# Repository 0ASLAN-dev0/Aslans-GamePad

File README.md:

# **Aslan's GamepPad**
## **Introduction**

This is a little macropad I made, It consists of a Xiao RP2040, Four  Cherry MX Switches and 2 RGB LEDs, Its basically a little rgb keyboard that consits of only four keys that i've coded to be WASD thou that can be changed from the code, The 2 RGB LEDs circle through the color wheel in a smooth animation and to give a sense of feedback each key is assigned a color that shows up when that key is pressed. Thats it :).

---

## **Required Parts**

1x Seeed XIAO RP2040 DIP,
4x Cherry MX-Style switches (Green preferably),
4x Blank DSA Keycaps,
2x SK6812 MINI-E LEDs,
4x M3x16mm screws,
1x 3D printed case (consists of two parts),
1x Soldering Iron/Kit,
1x PCB.

---

## **Images**

### **Render**

### **Schematic**

### **PCB**

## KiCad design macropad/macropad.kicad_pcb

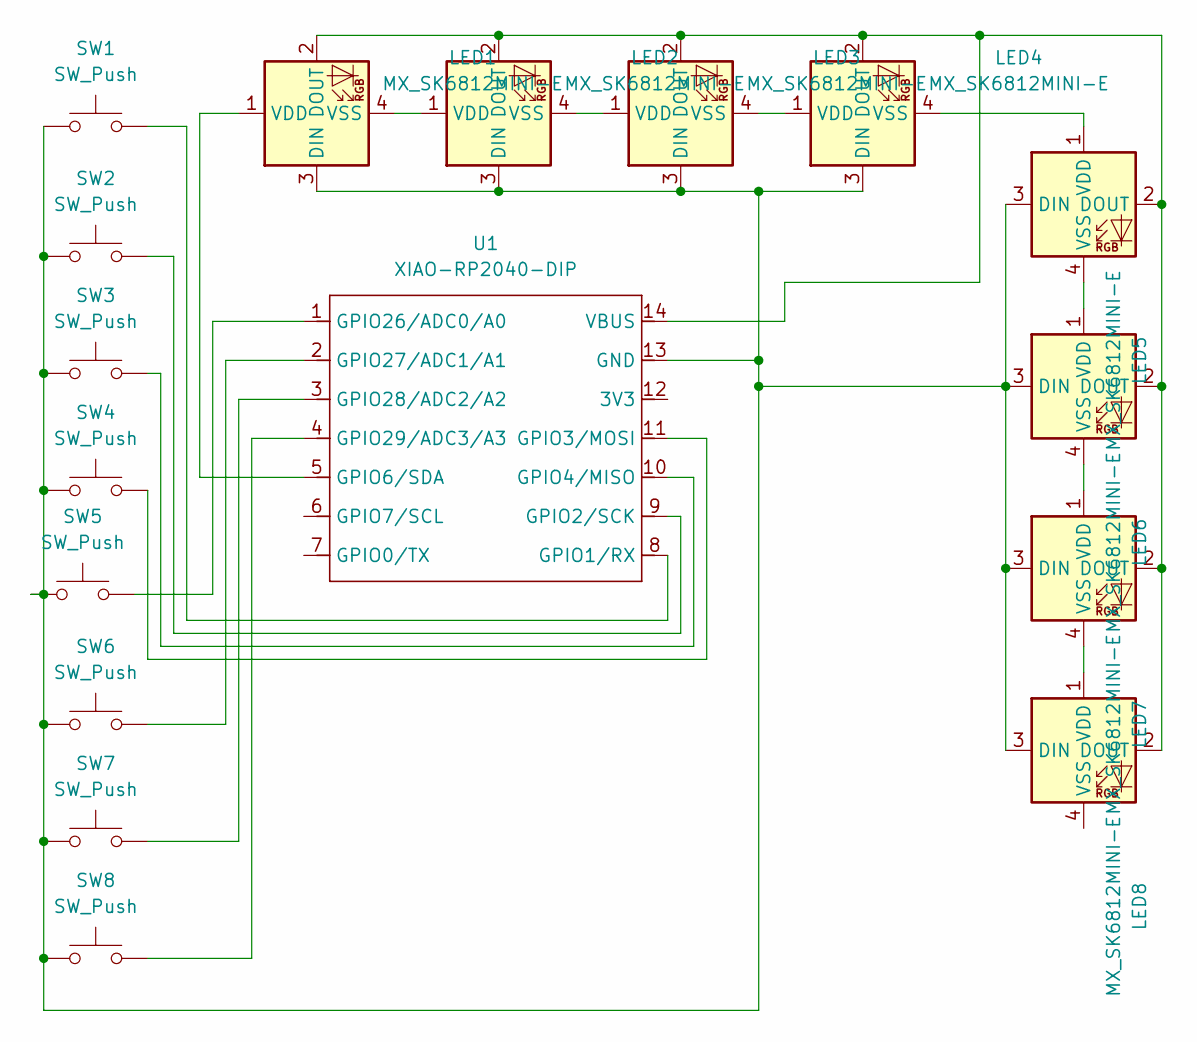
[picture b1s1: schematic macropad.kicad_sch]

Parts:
LED1, LED2, LED3, LED4, LED5, LED6, LED7, LED8: MX_SK6812MINI-E; LED_MX_6028R
SW1, SW2, SW3, SW4, SW5, SW6, SW7, SW8: SW_Push; SW_Cherry_MX_1.00u_PCB
U1: XIAO-RP2040-DIP

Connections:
unnamed: LED1.3 (DIN), LED2.3 (DIN), LED3.3 (DIN), LED4.3 (DIN), LED5.3 (DIN), LED6.3 (DIN), LED7.3 (DIN), LED8.3 (DIN), SW1.1, SW2.1, SW3.1, SW4.1, SW5.1, SW6.1, SW7.1, SW8.1, U1.13 (GND)
unnamed: LED1.2 (DOUT), LED2.2 (DOUT), LED3.2 (DOUT), LED4.2 (DOUT), LED5.2 (DOUT), LED6.2 (DOUT), LED7.2 (DOUT), LED8.2 (DOUT), U1.14 (VBUS)
unnamed: LED1.1 (VDD), U1.5 (GPIO6/SDA)
unnamed: LED1.4 (VSS), LED2.1 (VDD)
unnamed: LED2.4 (VSS), LED3.1 (VDD)
unnamed: LED3.4 (VSS), LED4.1 (VDD)
unnamed: LED4.4 (VSS), LED5.1 (VDD)
unnamed: LED5.4 (VSS), LED6.1 (VDD)
unnamed: LED6.4 (VSS), LED7.1 (VDD)
unnamed: LED7.4 (VSS), LED8.1 (VDD)
unnamed: SW1.2, U1.8 (GPIO1/RX)
unnamed: SW2.2, U1.9 (GPIO2/SCK)
unnamed: SW4.2, U1.11 (GPIO3/MOSI)
unnamed: SW3.2, U1.10 (GPIO4/MISO)
unnamed: SW5.2, U1.1 (GPIO26/ADC0/A0)
unnamed: SW6.2, U1.2 (GPIO27/ADC1/A1)
unnamed: SW7.2, U1.3 (GPIO28/ADC2/A2)
unnamed: SW8.2, U1.4 (GPIO29/ADC3/A3)

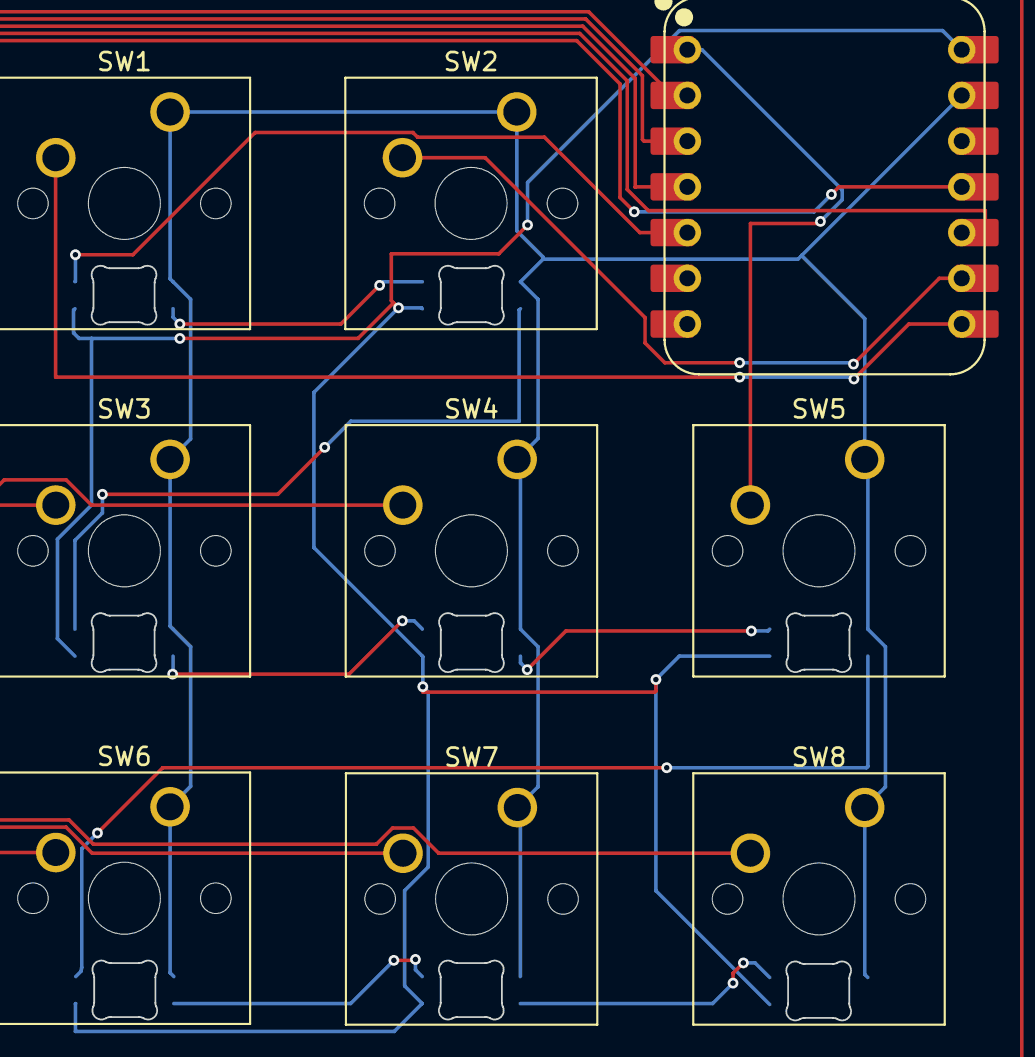
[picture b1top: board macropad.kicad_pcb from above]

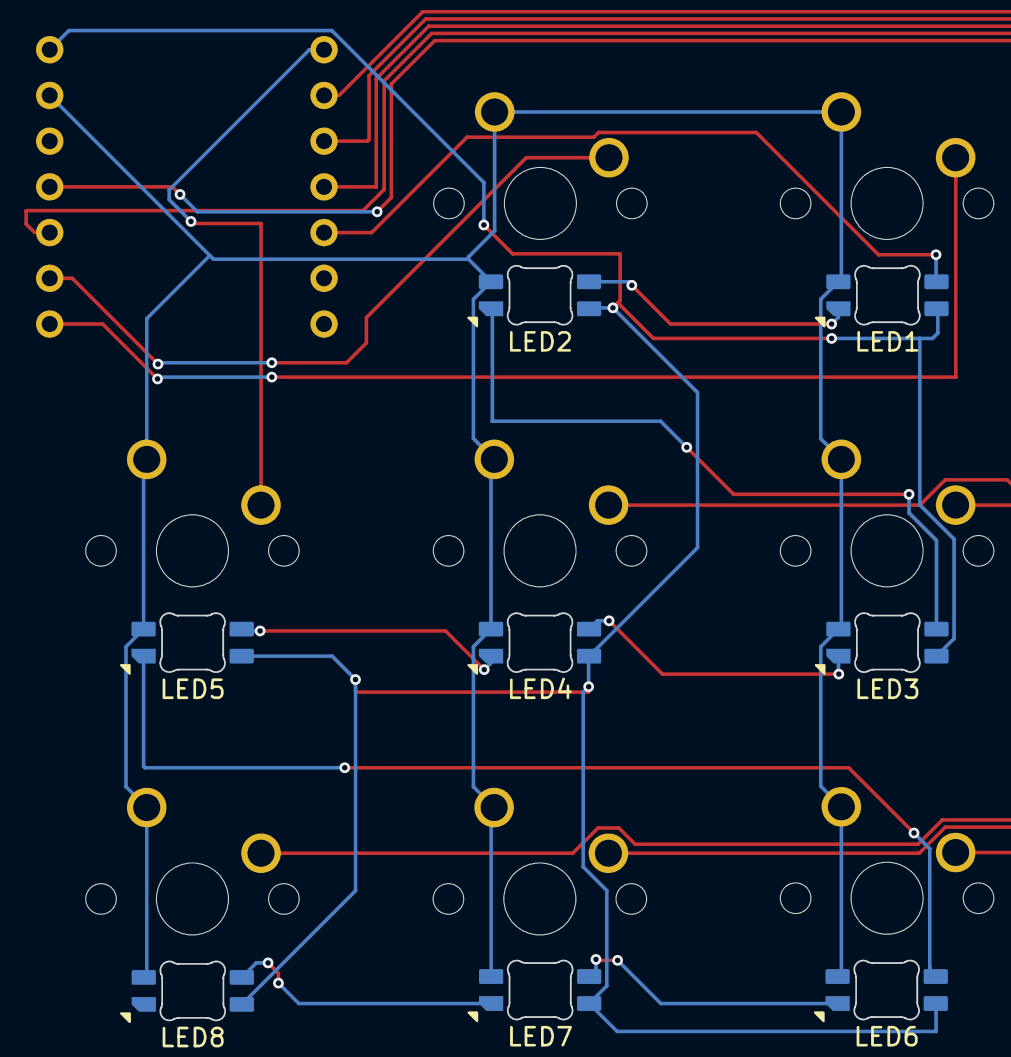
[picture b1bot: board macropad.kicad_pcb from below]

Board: 2 copper layers, 17 parts (8 on the bottom side), 18 nets.

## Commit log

2025-12-07 Refactor rainbow function and update LED colors
    Updated rainbow function to use HSV color space and adjusted LED color for key D.
2025-12-09 Refactor main.py for new button and LED configuration
    Updated button mapping and LED handling for a new setup with 8 buttons and a rainbow animation effect.
